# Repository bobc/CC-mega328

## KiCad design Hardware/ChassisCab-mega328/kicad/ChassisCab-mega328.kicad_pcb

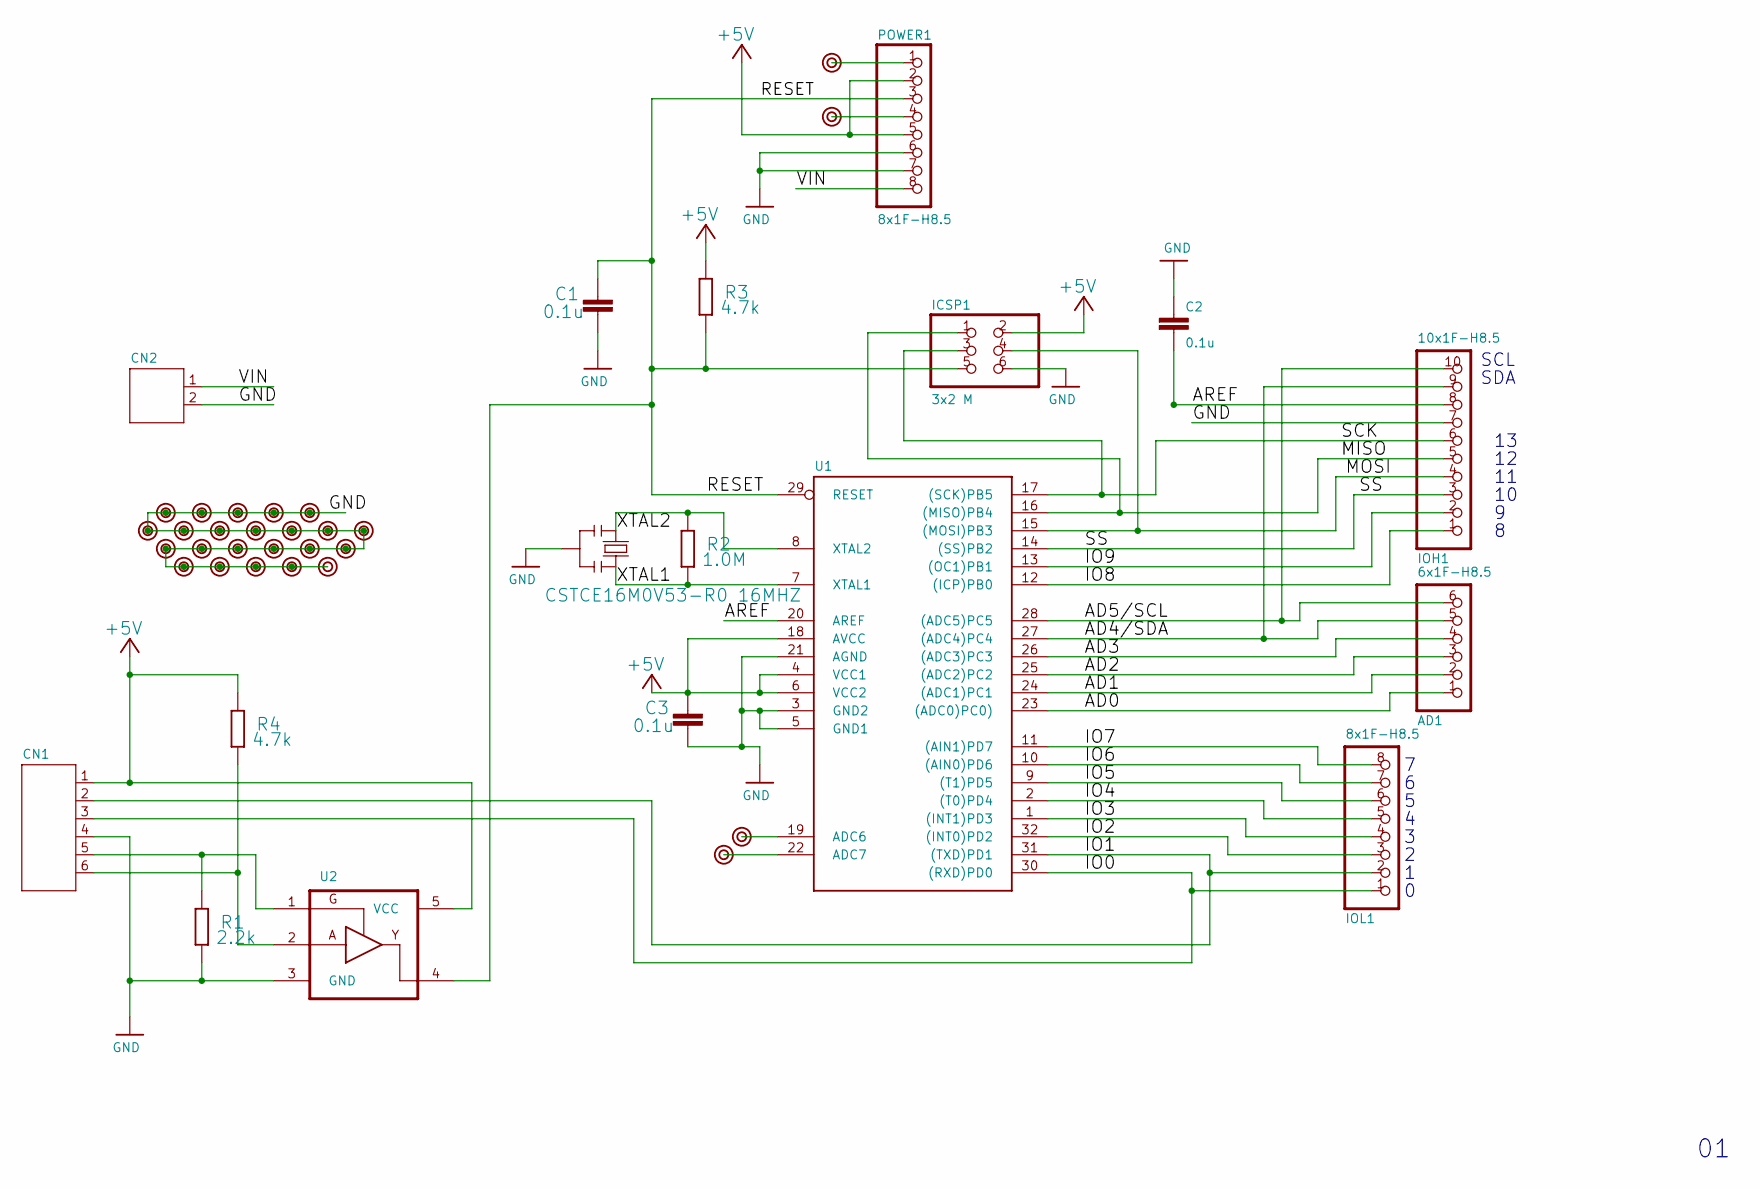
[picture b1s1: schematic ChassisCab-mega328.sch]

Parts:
AD1: 6x1F-H8.5; 1X06
C1, C2, C3: 0.1u; C0603
CN1: S6B-PH
CN2: S2B-XH
ICSP1: 3x2 M; 2X03
IOH1: 10x1F-H8.5; 1X10
IOL1: 8x1F-H8.5; 1X08
POWER1: 8x1F-H8.5; 1X08
R1: 2.2k; R0603
R2: 1.0M; R0603
R3, R4: 4.7k; R0603
U1: ATMEGA328P-AU; TQFP32
U2: TC7SZ126F; SMV
U$1, U$2, U$3, U$4, U$5, U$6, U$7, U$8, U$9, U$10, U$11, U$12, U$13, U$14, U$15, U$16, U$17, U$18, U$19, U$20, U$21, U$22, U$23, U$24, U$25, U$26, U$27: PAD
X1: CSTCE16M0V53-R0 16MHZ; CSTCE_V

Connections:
+5V: C3.2, CN1.1, ICSP1.2, POWER1.2, POWER1.5, R3.2, R4.2, U1.4 (VCC1), U1.6 (VCC2), U1.18 (AVCC), U2.5 (VCC)
AD0: AD1.1, U1.23 ((ADC0)PC0))
AD1: AD1.2, U1.24 ((ADC1)PC1)
AD2: AD1.3, U1.25 ((ADC2)PC2)
AD3: AD1.4, U1.26 ((ADC3)PC3)
AD4/SDA: AD1.5, IOH1.9, U1.27 ((ADC4)PC4)
AD5/SCL: AD1.6, IOH1.10, U1.28 ((ADC5)PC5)
AD6: U1.19 (ADC6), U$1.1
AD7: U1.22 (ADC7), U$2.1
AREF: C2.2, IOH1.8, U1.20 (AREF)
GND: C1.1, C2.1, C3.1, CN1.4, CN2.2, ICSP1.6, IOH1.7, POWER1.6, POWER1.7, R1.1, U1.3 (GND2), U1.5 (GND1), U1.21 (AGND), U2.3 (GND), U$3.1, U$4.1, U$5.1, U$6.1, U$7.1, U$8.1, U$9.1, U$10.1, U$11.1, U$12.1, U$13.1, U$14.1, U$15.1, U$16.1, U$17.1, U$18.1, U$19.1, U$20.1, U$21.1, U$22.1, U$23.1, U$24.1, U$27.1, X1.2
IO0: CN1.3, IOL1.1, U1.30 ((RXD)PD0)
IO1: CN1.2, IOL1.2, U1.31 ((TXD)PD1)
IO2: IOL1.3, U1.32 ((INT0)PD2)
IO3: IOL1.4, U1.1 ((INT1)PD3)
IO4: IOL1.5, U1.2 ((T0)PD4)
IO5: IOL1.6, U1.9 ((T1)PD5)
IO6: IOL1.7, U1.10 ((AIN0)PD6)
IO7: IOL1.8, U1.11 ((AIN1)PD7)
IO8: IOH1.1, U1.12 ((ICP)PB0)
IO9: IOH1.2, U1.13 ((OC1)PB1)
MISO: ICSP1.1, IOH1.5, U1.16 ((MISO)PB4)
MOSI: ICSP1.4, IOH1.4, U1.15 ((MOSI)PB3)
unnamed: CN1.5, R1.2, U2.1 (G)
unnamed: CN1.6, R4.1, U2.2 (A)
unnamed: POWER1.1, U$25.1
unnamed: POWER1.4, U$26.1
RESET: C1.2, ICSP1.5, POWER1.3, R3.1, U1.29 (RESET), U2.4 (Y)
SCK: ICSP1.3, IOH1.6, U1.17 ((SCK)PB5)
SS: IOH1.3, U1.14 ((SS)PB2)
VIN: CN2.1, POWER1.8
XTAL1: R2.1, U1.7 (XTAL1), X1.3
XTAL2: R2.2, U1.8 (XTAL2), X1.1

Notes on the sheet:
SDA
SCL

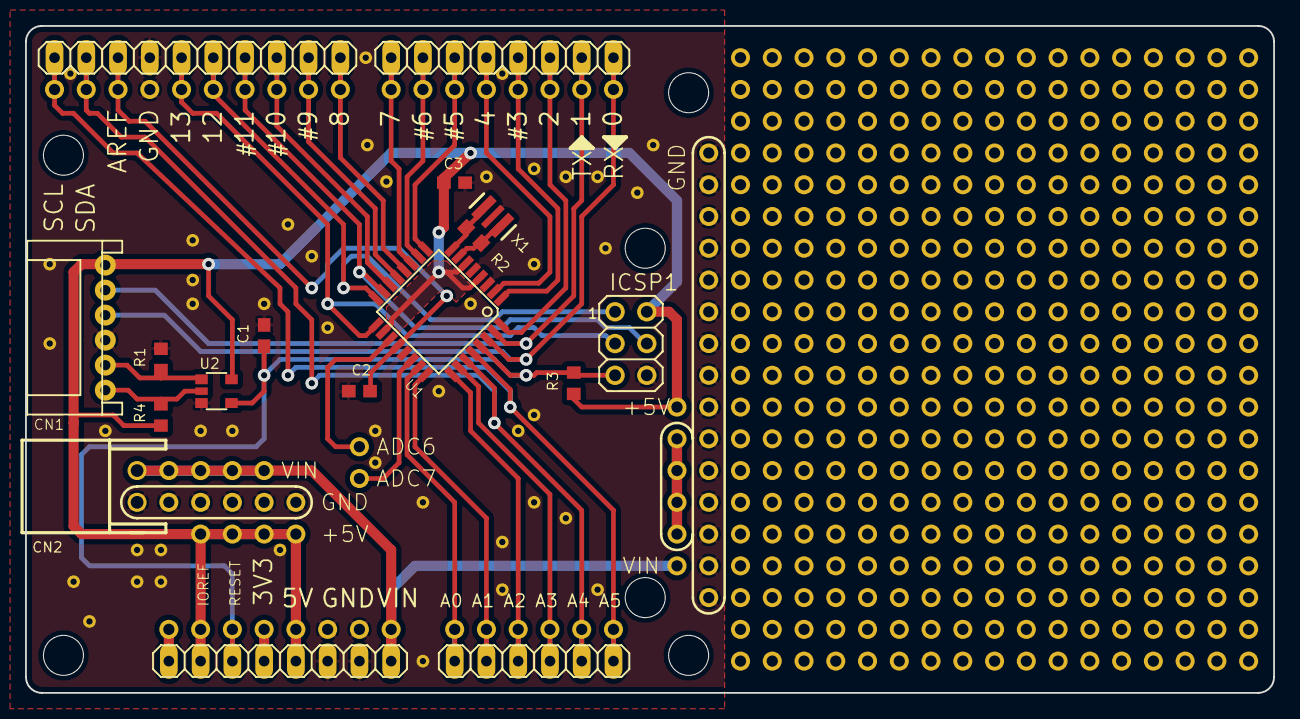
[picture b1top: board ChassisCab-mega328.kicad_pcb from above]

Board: 2 copper layers, 99.8 x 53.3 mm, 476 parts (0 on the bottom side), 33 nets.

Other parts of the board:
@HOLE1: @HOLE1
@HOLE2: @HOLE2
@HOLE3: @HOLE3
@HOLE4: @HOLE4
@HOLE5: @HOLE5
@HOLE6: @HOLE6
@V1: @V1
@V2: @V2
@V3: @V3
@V4: @V4
@V5: @V5
@V6: @V6
@V7: @V7
@V8: @V8
@V9: @V9
@V10: @V10
@V11: @V11
@V12: @V12
@V13: @V13
@V14: @V14
@V15: @V15
@V16: @V16
@V17: @V17
@V18: @V18
@V19: @V19
@V20: @V20
@V21: @V21
@V22: @V22
@V23: @V23
@V24: @V24
@V25: @V25
@V26: @V26
@V27: @V27
@V28: @V28
@V29: @V29
@V30: @V30
@V31: @V31
@V32: @V32
@V33: @V33
@V34: @V34
@V35: @V35
@V36: @V36
@V37: @V37
@V38: @V38
@V39: @V39
@V40: @V40
@V41: @V41
@V42: @V42
@V43: @V43
@V44: @V44
@V45: @V45
@V46: @V46
@V47: @V47
@V48: @V48
@V49: @V49
@V50: @V50
@V51: @V51
@V52: @V52
@V53: @V53
@V54: @V54
@V55: @V55
@V56: @V56
@V57: @V57
@V58: @V58
@V59: @V59
@V60: @V60
@V61: @V61
@V62: @V62
@V63: @V63
@V64: @V64
@V65: @V65
@V66: @V66
@V67: @V67
@V68: @V68
@V69: @V69
@V70: @V70
@V71: @V71
@V72: @V72
@V73: @V73
@V74: @V74
@V75: @V75
@V76: @V76
@V77: @V77
@V78: @V78
@V79: @V79
@V80: @V80
@V81: @V81
@V82: @V82
@V83: @V83
@V84: @V84
@V85: @V85
@V86: @V86
@V87: @V87
@V88: @V88
@V89: @V89
@V90: @V90
@V91: @V91
@V92: @V92
@V93: @V93
@V94: @V94
@V95: @V95
@V96: @V96
@V97: @V97
@V98: @V98
@V99: @V99
@V100: @V100
@V101: @V101
@V102: @V102
@V103: @V103
@V104: @V104
@V105: @V105
@V106: @V106
@V107: @V107
@V108: @V108
@V109: @V109
@V110: @V110
@V111: @V111
@V112: @V112
@V113: @V113
@V114: @V114
@V115: @V115
@V116: @V116
@V117: @V117
@V118: @V118
@V119: @V119
@V120: @V120
@V121: @V121
@V122: @V122
@V123: @V123
@V124: @V124
@V125: @V125
@V126: @V126
@V127: @V127
@V128: @V128
@V129: @V129
@V130: @V130
@V131: @V131
@V132: @V132
@V133: @V133
@V134: @V134
@V135: @V135
@V136: @V136
@V137: @V137
@V138: @V138
@V139: @V139
@V140: @V140
@V141: @V141
@V142: @V142
@V143: @V143
@V144: @V144
@V145: @V145
@V146: @V146
@V147: @V147
@V148: @V148
@V149: @V149
@V150: @V150
@V151: @V151
@V152: @V152
@V153: @V153
@V154: @V154
@V155: @V155
@V156: @V156
@V157: @V157
@V158: @V158
@V159: @V159
@V160: @V160
@V161: @V161
@V162: @V162
@V163: @V163
@V164: @V164
@V165: @V165
@V166: @V166
@V167: @V167
@V168: @V168
@V169: @V169
@V170: @V170
@V171: @V171
@V172: @V172
@V173: @V173
@V174: @V174
@V175: @V175
@V176: @V176
@V177: @V177
@V178: @V178
@V179: @V179
@V180: @V180
@V181: @V181
@V182: @V182
@V183: @V183
@V184: @V184
@V185: @V185
@V186: @V186
@V187: @V187
@V188: @V188
@V189: @V189
@V190: @V190
@V191: @V191
@V192: @V192
@V193: @V193
@V194: @V194
@V195: @V195
@V196: @V196
@V197: @V197
@V198: @V198
@V199: @V199
@V200: @V200
@V201: @V201
@V202: @V202
@V203: @V203
@V204: @V204
@V205: @V205
@V206: @V206
@V207: @V207
@V208: @V208
@V209: @V209
@V210: @V210
@V211: @V211
@V212: @V212
@V213: @V213
@V214: @V214
@V215: @V215
@V216: @V216
@V217: @V217
@V218: @V218
@V219: @V219
@V220: @V220
@V221: @V221
@V222: @V222
@V223: @V223
@V224: @V224
@V225: @V225
@V226: @V226
@V227: @V227
@V228: @V228
@V229: @V229
@V230: @V230
@V231: @V231
@V232: @V232
@V233: @V233
@V234: @V234
@V235: @V235
@V236: @V236
@V237: @V237
@V238: @V238
@V239: @V239
@V240: @V240
@V241: @V241
@V242: @V242
@V243: @V243
@V244: @V244
@V245: @V245
@V246: @V246
@V247: @V247
@V248: @V248
@V249: @V249
@V250: @V250
@V251: @V251
@V252: @V252
@V253: @V253
@V254: @V254
@V255: @V255
@V256: @V256
@V257: @V257
@V258: @V258
@V259: @V259
@V260: @V260
@V261: @V261
@V262: @V262
@V263: @V263
@V264: @V264
@V265: @V265
@V266: @V266
@V267: @V267
@V268: @V268
@V269: @V269
@V270: @V270
@V271: @V271
@V272: @V272
@V273: @V273
@V274: @V274
@V275: @V275
@V276: @V276
@V277: @V277
@V278: @V278
@V279: @V279
@V280: @V280
@V281: @V281
@V282: @V282
@V283: @V283
@V284: @V284
@V285: @V285
@V286: @V286
@V287: @V287
@V288: @V288
@V289: @V289
@V290: @V290
@V291: @V291
@V292: @V292
@V293: @V293
@V294: @V294
@V295: @V295
@V296: @V296
@V297: @V297
@V298: @V298
@V299: @V299
@V300: @V300
@V301: @V301
@V302: @V302
@V303: @V303
@V304: @V304
@V305: @V305
@V306: @V306
@V307: @V307
@V308: @V308
@V309: @V309
@V310: @V310
@V311: @V311
@V312: @V312
@V313: @V313
@V314: @V314
@V315: @V315
@V316: @V316
@V317: @V317
@V318: @V318
@V319: @V319
@V320: @V320
@V321: @V321
@V322: @V322
@V323: @V323
@V324: @V324
@V325: @V325
@V326: @V326
@V327: @V327
@V328: @V328
@V329: @V329
@V330: @V330
@V331: @V331
@V332: @V332
@V333: @V333
@V334: @V334
@V335: @V335
@V336: @V336
@V337: @V337
@V338: @V338
@V339: @V339
@V340: @V340
@V341: @V341
@V342: @V342
@V343: @V343
@V344: @V344
@V345: @V345
@V346: @V346
@V347: @V347
@V348: @V348
@V349: @V349
@V350: @V350
@V351: @V351
@V352: @V352
@V353: @V353
@V354: @V354
@V355: @V355
@V356: @V356
@V357: @V357
@V358: @V358
@V359: @V359
@V360: @V360
@V361: @V361
@V362: @V362
@V363: @V363
@V364: @V364
@V365: @V365
@V366: @V366
@V367: @V367
@V368: @V368
@V369: @V369
@V370: @V370
@V371: @V371
@V372: @V372
@V373: @V373
@V374: @V374
@V375: @V375
@V376: @V376
@V377: @V377
@V378: @V378
@V379: @V379
@V380: @V380
@V381: @V381
@V382: @V382
@V383: @V383
@V384: @V384
@V385: @V385
@V386: @V386
@V387: @V387
@V388: @V388
@V389: @V389
@V390: @V390
@V391: @V391
@V392: @V392
@V393: @V393
@V394: @V394
@V395: @V395
@V396: @V396
@V397: @V397
@V398: @V398
@V399: @V399
@V400: @V400
@V401: @V401
@V402: @V402
@V403: @V403
@V404: @V404
@V405: @V405
@V406: @V406
@V407: @V407
@V408: @V408
@V409: @V409
@V410: @V410
@V411: @V411
@V412: @V412
@V413: @V413
@V414: @V414
@V415: @V415
@V416: @V416
@V417: @V417
@V418: @V418
@V419: @V419
@V420: @V420
@V421: @V421
@V422: @V422
@V423: @V423
@V424: @V424
@V425: @V425
@V426: @V426

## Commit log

2017-06-13 Consversion to KiCad
